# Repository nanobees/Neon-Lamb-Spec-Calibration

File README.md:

# Neon-Lamb-Spec-Calibration
A Neon Lamb Circuit for Calibrating the Optical Spectroscopy System of Our Lab

This easy circuit is designed for calibrating the optical spectroscopy system of our lab. The spectroscopy system is built
with a Newport Monochromator, an f/# matcher and a photodetector with a DAQ card for data acquisiton. In order to ensure 
that we take scientifically accurate data, we use neon lamb which has a well defined spectrum.

For further information please contact with me; haltugyildirim_at_protonmail.com

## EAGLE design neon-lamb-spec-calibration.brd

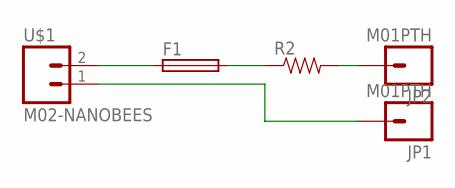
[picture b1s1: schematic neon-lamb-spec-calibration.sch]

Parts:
F1: GSH15
JP1, JP2: M01PTH; 1X01
R2: RESISTORPTH-1W; AXIAL-0.6
U$1: M02-NANOBEES

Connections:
unnamed: F1.1, U$1.2
unnamed: JP2.1, R2.P$2 (2)
unnamed: JP1.1, U$1.1
unnamed: F1.2, R2.P$1 (1)

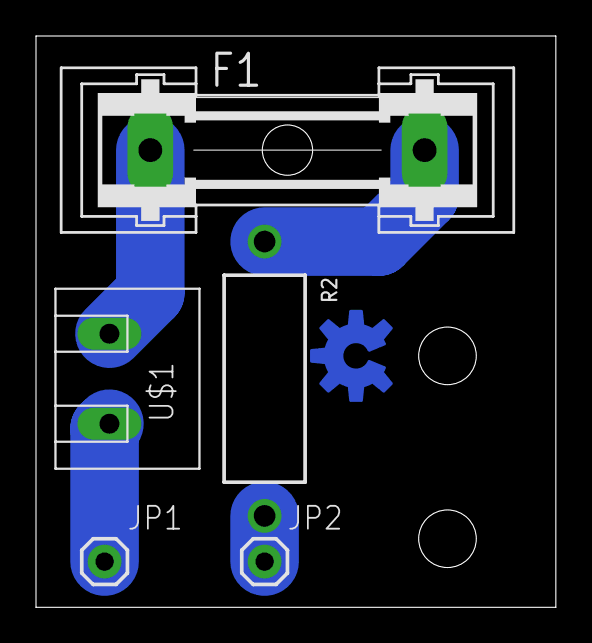
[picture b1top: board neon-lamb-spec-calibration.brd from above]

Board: 2 copper layers, 28.9 x 31.7 mm, 6 parts (0 on the bottom side), 4 nets.

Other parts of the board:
U$2: OSHW-LOGO-M

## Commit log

2016-08-26 initial design files
    initial add
2016-08-27 adding sample data and finished product jpg
    add files

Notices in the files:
parts and their libraries:
SparkFun-Connectors: Licensing: Creative Commons ShareAlike 4.0 International - https://creativecommons.org/licenses/by-sa/4.0
